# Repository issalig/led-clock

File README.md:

led-clock
=========

Clock adventures with a led matrix and more fun.

After thinking about the simplest way to build a word clock I experimented with hand-soldered led matrices, 74HC595, 7219 and others to end up with the mighty 7219 and 8x8 led matrices.

7219 works with common cathode displays but a nice workaround to make it work with common anode matrices is to interchange rows by cols (transposing the matrix) and do the same (transposing it again) from software. Anyway, the PCB has been designed to support both c.c. and c.a. as well as 3mm matrices.

As led matrices did not seemed the only thing to play with in 5x5 cm2, the board now includes weather sensors, FM radio and I2C, SPI connectivity, servo connectors, ...

Board features
--------------

  - Led matrix 8x8 5mm common cathode or anode
  - 2 buttons
  - Small factor 5cmx5cm (fits in cheap PCB manufacturing)
  - Exported I2C, SPI and Analog pins
  - Chainable (1 or more matrices)
  - Support for common cathode and common anode
  - Arduino Nano
  - Max7219
  - RTC DS1307
  - Nokia LCD
  - TFT
  - Humidity sensor DHT11
  - Pressure sensor BMP180
  - TEA5767 FM Radio
  - LDR sensor
  - RGB Led
  - IR 1838
  - Exported servo-like connectors.

Software
--------

  Arduino has been chosen as the development environment due to the available libraries and its simplicity. MSP430 has been also considered but I was not able to make it work. Any volunteer?

  Operation modes:
  -Sleep. Wake up when button is touched
  -Alarm.

Clock layout
------------

  The idea is to have different interchangeable covers allowing the clock to easily change its appearance (and behaviour).
  Some ideas are:
  
- word clock
  Consists of a grid of characters that contain the words for telling the time in natural language.
      
- number/symbol clock
  Consists of a grid with digits and some extra symbols to indicate weather, moon, etc, ...
      
- calendar
  Consists of a grid with days of week, month, weather, ... (mark first of month to calculate number of day)
	  
- anyclock
    Feel free to design your own clock, just represent your info in 64 elements (or more)

TODO
----
  
- 3.3v and 5v on board (OK)
	http://lowpowerlab.com/blog/2014/03/13/moteino-power-shield-now-available/
	- 2 button
		1 is mode: sleep, set hour, 
		1 is set:  +1, next option
	- 3 button	
    - buzzer connection  //1M resistor ??? just servo/generic connector (-+S)
	- remote connection // risk, interference with voltage, just connector(-+S)
	- xronos clock (how they manage buttons, eeprom)

	- Documentation for pinout

	- (OK) Possibility of adding capes, I2C, etc..
    - (OK) Pinout assignment and reserved pins

 - changes for 0.4b
 	- group components by function
 	- more separation on transistor
 	- check transistor footprint and type
 	- align connectors on edge (aesthetics)
 	- check button footprint ovaled hole and pin space
 	- common interface for LCD and TFT, check pinouts and models
	- bigger TFT? explore it.
        - silkscreen on back for headers pluging on back (such as screens, martices, ...)

  - Software  
    - Grid data structure for symbols    
    - Grid editor http://jsfiddle.net/issalig/2h4wjbmL/
    
  - Case
    - Carboard, bands and needles. Easy to change front mask cover
    - Wood. (Anyone with a laser cutter/CNC?)
 
 - Masks
    - word, temperature, humidex, calendar, spectrum analyzer
    - rotating wheel and servo?
 - Capes

Light programming	
https://github.com/szczys/Light-Programmer
http://www.wayneandlayne.com/projects/blinky/design/
https://github.com/mossblaser/Clockie  look for better timing in js (requestAnimationFrame?) up to 60hz http://creativejs.com/resources/requestanimationframe/
http://jsfiddle.net/paul/rjbGw/3/
If is up to 60hz, should be sampled at 120Hz from arduino side. 64bytes will take around 10s
https://github.com/mchr3k/arduino-libs-manchester/blob/master/Manchester.cpp

//people playing with matrices
http://www.gammon.com.au/forum/?id=11516

//adafruit has also a word clock :D
https://github.com/andydoro/WordClock-NeoMatrix8x8/tree/master/WordClock_NeoMatrix8x8

https://github.com/formatc1702/Micro-Word-Clock/

http://forum.arduino.cc/index.php?topic=118338.60
https://github.com/mirkin/pi-word-clock

//nokia
http://www.ardumania.es/lcd-grafico-de-84x48/ (old pinout)
http://www.instructables.com/id/Nokia-5110-graphics-tutorial/?ALLSTEPS
reconsider transistor. check lcd board if already have one (seems not).
reconsider share tft pinout
3.3v VCC and 3v com signals
20mA x 4 leds need transistor not to burn signal pin (max 20mA) ppl says 330ohm is enough
https://learn.sparkfun.com/tutorials/graphic-lcd-hookup-guide //about resistors

//sunrise
https://gist.github.com/jamesabruce/8112785
https://svn.kapsi.fi/jpa/led-controller/sw/src/led_task.c

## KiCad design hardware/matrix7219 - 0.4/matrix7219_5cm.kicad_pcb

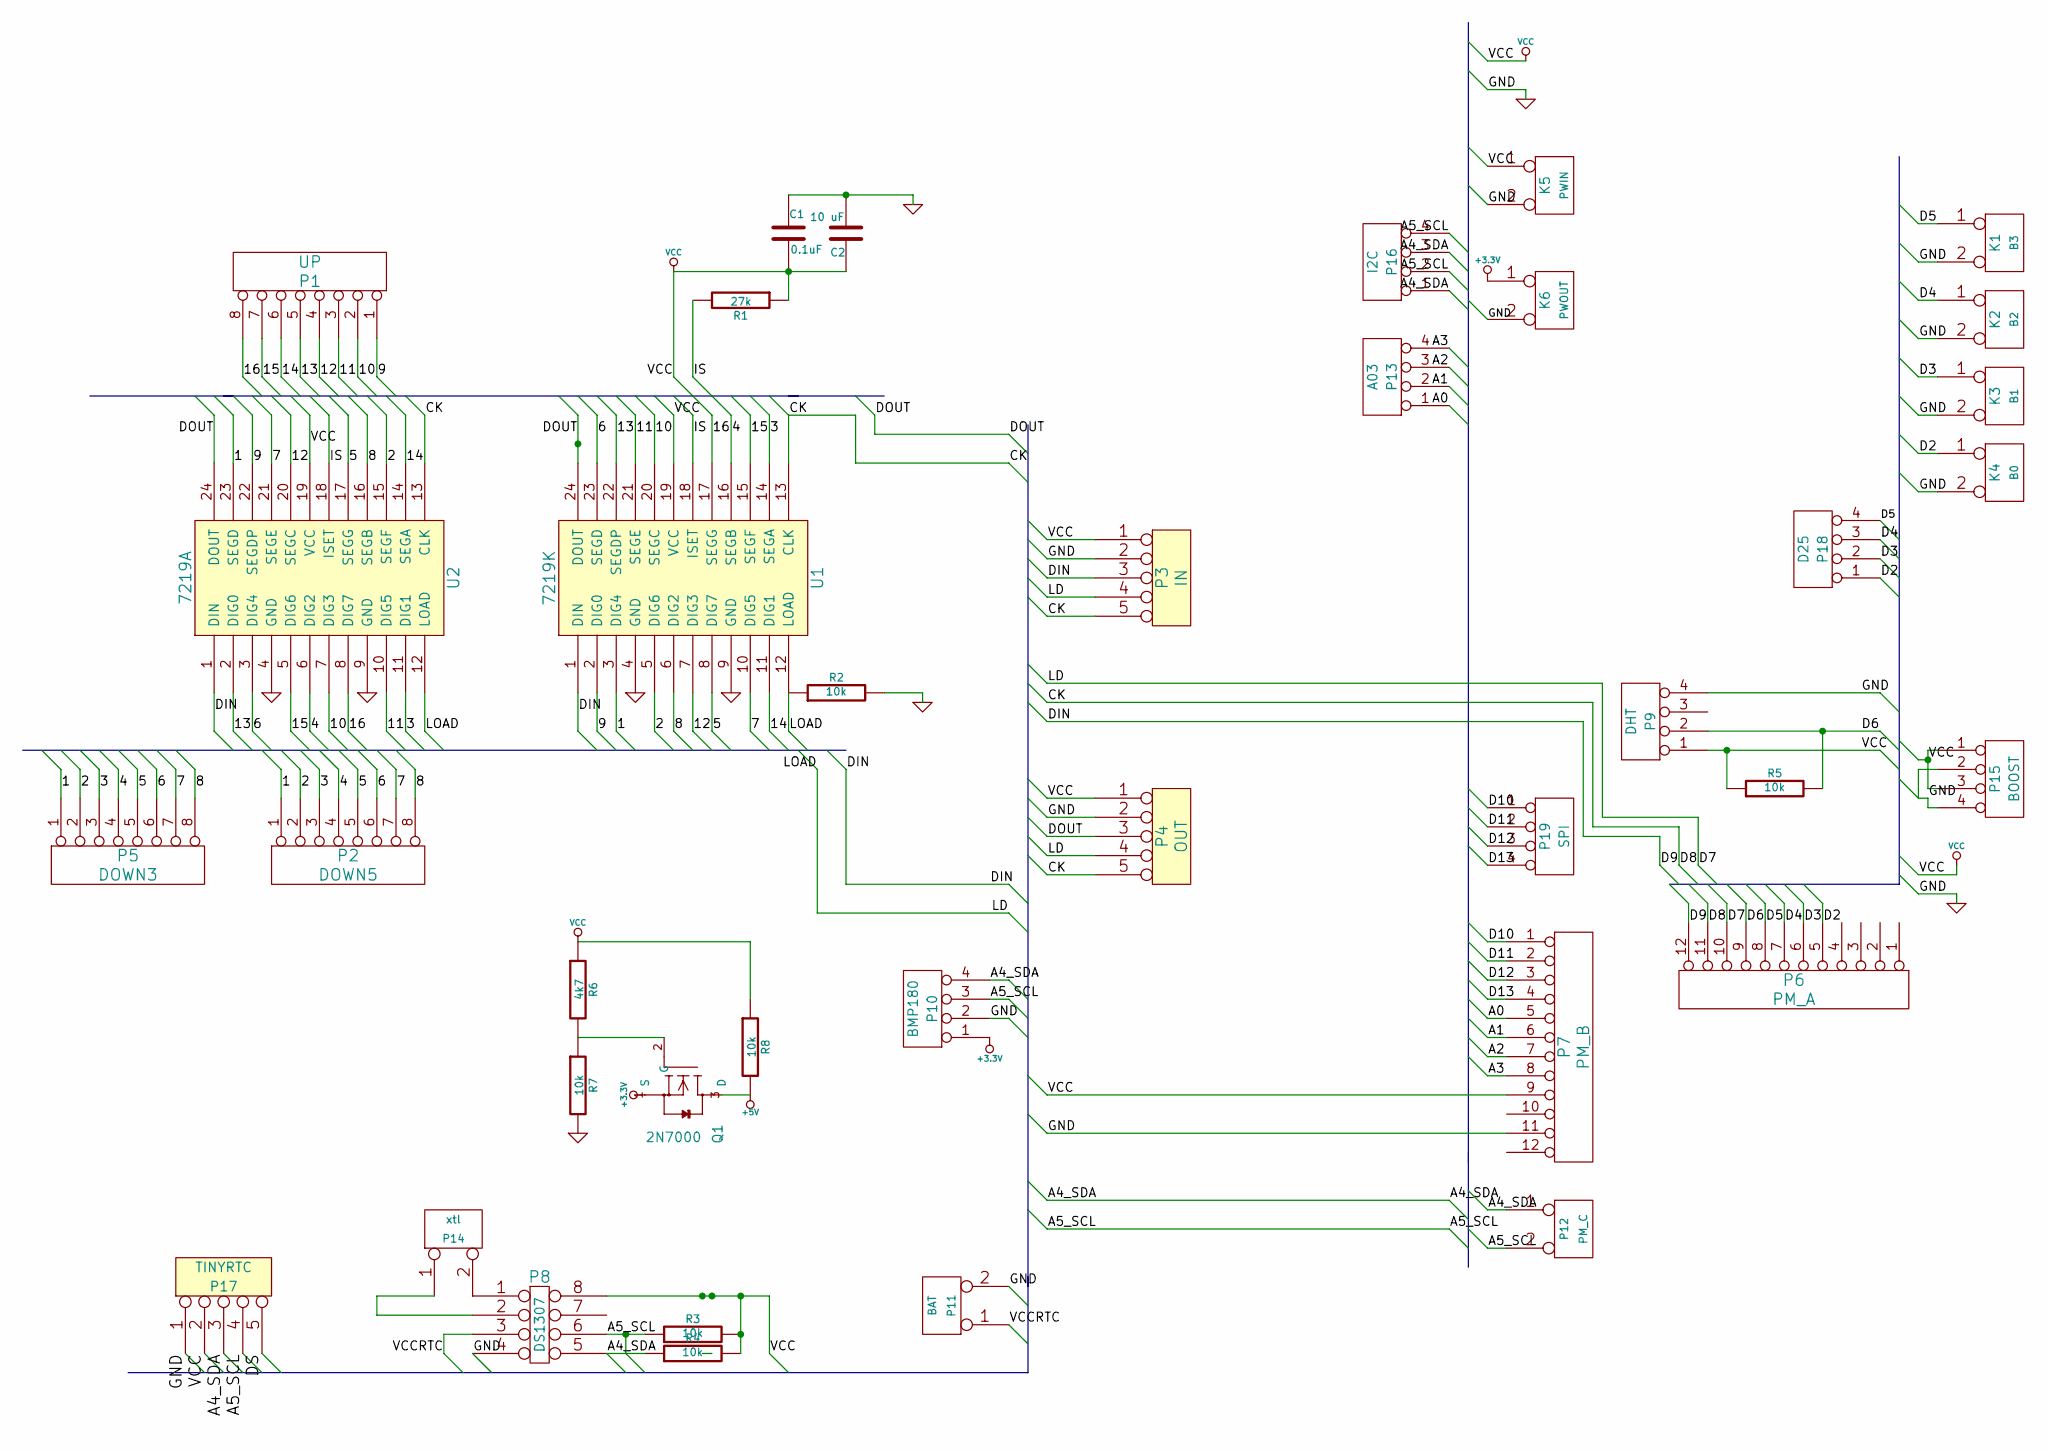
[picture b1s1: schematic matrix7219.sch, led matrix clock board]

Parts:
C1: 0.1uF
C2: 10 uF
K1: B3
K2: B2
K3: B1
K4: B0
K5: PWIN
K6: PWOUT
P1: UP
P2: DOWN5
P3: IN
P4: OUT
P5: DOWN3
P6: PM_A
P7: PM_B
P8: DS1307
P9: DHT
P10: BMP180
P11: BAT
P12: PM_C
P13: A03
P14: xtl
P15: BOOST
P16: I2C
P17: TINYRTC
P18: D25
P19: SPI
Q1: 2N7000; m-pad-2.1-TO92
R1: 27k
R2, R3, R4, R5, R7, R8: 10k
R6: 4k7
U1: 7219K
U2: 7219A

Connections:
+3.3V: K6.1, P10.1, Q1.1 (S)
+5V: Q1.3 (D), R8.2
/1: P2.1, P5.1, U1.3 (DIG4), U2.23 (SEGD)
/2: P2.2, P5.2, U1.5 (DIG6), U2.15 (SEGF)
/3: P2.3, P5.3, U1.14 (SEGA), U2.11 (DIG1)
/4: P2.4, P5.4, U1.16 (SEGB), U2.6 (DIG2)
/5: P2.5, P5.5, U1.8 (DIG7), U2.17 (SEGG)
/6: P2.6, P5.6, U1.23 (SEGD), U2.3 (DIG4)
/7: P2.7, P5.7, U1.10 (DIG5), U2.21 (SEGE)
/8: P2.8, P5.8, U1.6 (DIG2), U2.16 (SEGB)
/9: P1.1, U1.2 (DIG0), U2.22 (SEGDP)
/10: P1.2, U1.20 (SEGC), U2.7 (DIG3)
/11: P1.3, U1.21 (SEGE), U2.10 (DIG5)
/12: P1.4, U1.7 (DIG3), U2.20 (SEGC)
/13: P1.5, U1.22 (SEGDP), U2.2 (DIG0)
/14: P1.6, U1.11 (DIG1), U2.14 (SEGA)
/15: P1.7, U1.15 (SEGF), U2.5 (DIG6)
/16: P1.8, U1.17 (SEGG), U2.8 (DIG7)
/A0: P7.5, P13.1
/A1: P7.6, P13.2
/A2: P7.7, P13.3
/A3: P7.8, P13.4
/A4_SDA: P8.5, P10.4, P12.1, P16.1, P16.3, P17.3, R4.1
/A5_SCL: P8.6, P10.3, P12.2 (PM), P16.2, P16.4, P17.4, R3.1
/CK: P3.5, P4.5, P6.11, U1.13 (CLK), U2.13 (CLK)
/D2: K4.1, P6.5, P18.1
/D3: K3.1, P6.6, P18.2
/D4: K2.1, P6.7, P18.3
/D5: K1.1, P6.8, P18.4
/D6: P6.9, P9.2, R5.2
/D7: P3.4, P4.4, P6.10, R2.1, U1.12 (LOAD), U2.12 (LOAD)
/D9: P3.3, P6.12, U1.1 (DIN), U2.1 (DIN)
/D10: P7.1, P19.1
/D11: P7.2, P19.2
/D12: P7.3, P19.3
/D13: P7.4, P19.4
/DOUT: P4.3, U1.24 (DOUT), U2.24 (DOUT)
/IS: R1.2, U1.18 (ISET), U2.18 (ISET)
/VCCRTC: P8.3, P11.1
GND: C1.1, C2.2, K1.2 (PM), K2.2 (PM), K3.2 (PM), K4.2 (PM), K5.2 (PM), K6.2 (PM), P3.2, P4.2, P7.11, P8.4, P9.4, P10.2, P11.2 (PM), P15.2, P15.4, P17.1, R2.2, R7.2, U1.4 (GND), U1.9 (GND), U2.4 (GND), U2.9 (GND)
unnamed: P8.1, P14.2 (PM)
unnamed: P8.2, P14.1
unnamed: Q1.2 (G), R6.2, R7.1
VCC: C1.2, C2.1, K5.1, P3.1, P4.1, P7.9, P8.8, P9.1, P15.1, P15.3, P17.2, R1.1, R3.2, R4.2, R5.1, R6.1, R8.1, U1.19 (VCC), U2.19 (VCC)

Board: 2 copper layers, 38 parts (2 on the bottom side), 44 nets, no tracks yet.

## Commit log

2014-07-13 :circus_tent: Added .gitattributes & .gitignore files
2014-07-13 dir strcuture
2014-07-13 arduino scripts
2014-07-13 cleaning files
2014-07-14 refactoring and cleanup
2014-07-14 renamed
2014-12-14 Hardware folder
    Kicad files
2014-12-19 Updated readme
    Updated readme
2015-01-08 updated docs
    pinout, readme
2015-01-11 updated docs
    updated docs
2015-01-12 updated layouts
    new layouts
2015-02-11 wip
    wip
2015-03-14 cleaning
    cleaning files
2015-11-05 Create es_words_several_layouts.txt
    Maybe useful for TFT or 2 8x8 matrices
2015-11-08 new name
2015-11-21 renamed docs
2015-11-21 clock layout
2015-11-21 libraries
2015-11-21 multiple 7219 devices
2015-11-21 power saving
2015-11-22 masks in eeprom and meteo funcs
2015-11-23 buttons
2015-11-25 refactor
2015-11-26 renaming defs
2015-11-29 simple pressure functions
2015-11-29 pressure
2017-02-06 hex changes
2017-02-07 hex version with buttons
2017-02-07 adapted to esp8266
2017-02-07 sleep mode changes
2017-02-08 hex fixes but still not working
2017-02-08 rtc fixes, proper render of time
2017-02-08 masks
2017-02-08 leds working, just a little bit more work
